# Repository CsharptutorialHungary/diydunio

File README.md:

# diydunio

A home makeable Arduino Uno clone

Part list: [parts.txt](parts.txt)

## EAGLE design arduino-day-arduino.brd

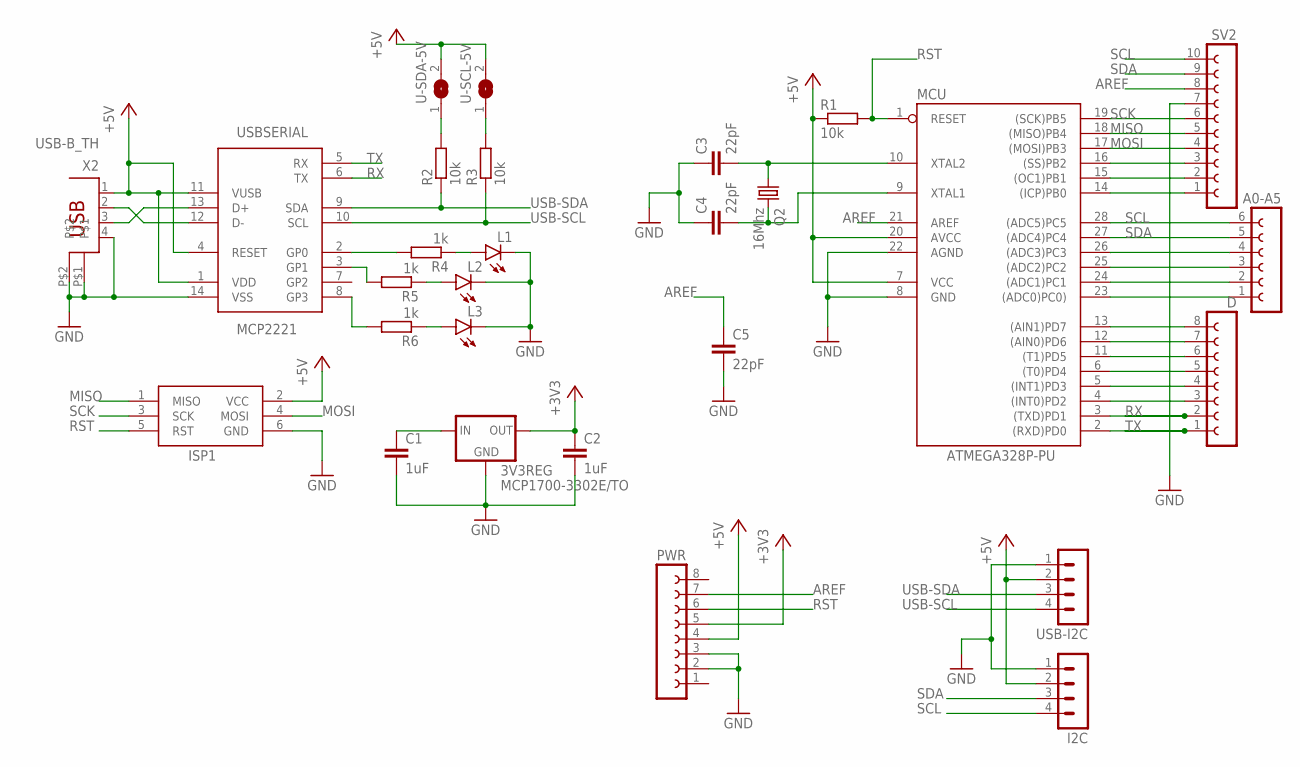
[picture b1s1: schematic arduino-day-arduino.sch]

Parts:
3V3REG: MCP1700-3302E/TO; TO92
A0-A5: FE06-1; FE06
C1, C2: 1uF; C025-025X050
C3, C4, C5: 22pF; C025-025X050
D: FE08-1; FE08
I2C: MA04-1
ISP1: AVRISP-6; AVRISP
L1, L2, L3: LED3MM
MCU: ATMEGA328P-PU; DIL28-3
PWR: FE08-1; FE08
Q2: 16Mhz; HC49/S
R1, R2, R3: 10k; 0204/7
R4, R5, R6: 1k; 0204/7
SV2: FE10-1; FE10
U-SCL-5V: SJW
U-SDA-5V: SJW
USB-I2C: MA04-1
USBSERIAL: MCP2221; DIL14
X2: USB-B_TH; PN61729

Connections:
+3V3: 3V3REG.3 (OUT), C2.1, PWR.5
+5V: I2C.2, ISP1.2 (VCC), MCU.7 (VCC), MCU.20 (AVCC), PWR.4, R1.1, U-SCL-5V.2, U-SDA-5V.2, USB-I2C.2, USBSERIAL.1 (VDD), USBSERIAL.4 (RESET), USBSERIAL.11 (VUSB), X2.1
AREF: C5.1, MCU.21 (AREF), PWR.7, SV2.8
GND: 3V3REG.1 (GND), C1.2, C2.2, C3.1, C4.1, C5.2, I2C.1, ISP1.6 (GND), L1.K (C), L2.K (C), L3.K (C), MCU.8 (GND), MCU.22 (AGND), PWR.2, PWR.3, SV2.7, USB-I2C.1, USBSERIAL.14 (VSS), X2.4, X2.P$1, X2.P$2
LED_RX: R4.2, USBSERIAL.2 (GP0)
LED_TX: R5.2, USBSERIAL.3 (GP1)
MISO: ISP1.1 (MISO), MCU.18 ((MISO)PB4), SV2.5
MOSI: ISP1.4 (MOSI), MCU.17 ((MOSI)PB3), SV2.4
unnamed: 3V3REG.2 (IN), C1.1
unnamed: D.3, MCU.4 ((INT0)PD2)
unnamed: D.4, MCU.5 ((INT1)PD3)
unnamed: D.5, MCU.6 ((T0)PD4)
unnamed: D.6, MCU.11 ((T1)PD5)
unnamed: D.7, MCU.12 ((AIN0)PD6)
unnamed: D.8, MCU.13 ((AIN1)PD7)
unnamed: A0-A5.1, MCU.23 ((ADC0)PC0))
unnamed: A0-A5.2, MCU.24 ((ADC1)PC1)
unnamed: A0-A5.3, MCU.25 ((ADC2)PC2)
unnamed: A0-A5.4, MCU.26 ((ADC3)PC3)
unnamed: MCU.14 ((ICP)PB0), SV2.1
unnamed: MCU.15 ((OC1)PB1), SV2.2
unnamed: MCU.16 ((SS)PB2), SV2.3
unnamed: R2.2, U-SDA-5V.1
unnamed: R3.2, U-SCL-5V.1
unnamed: USBSERIAL.12 (D-), X2.2
unnamed: USBSERIAL.13 (D+), X2.3
unnamed: L1.A, R4.1
unnamed: L2.A, R5.1
unnamed: L3.A, R6.1
unnamed: R6.2, USBSERIAL.8 (GP3)
unnamed: C3.2, MCU.10 (XTAL2), Q2.1
unnamed: C4.2, MCU.9 (XTAL1), Q2.2
RST: ISP1.5 (RST), MCU.1 (RESET), PWR.6, R1.2
RX: D.2, MCU.3 ((TXD)PD1), USBSERIAL.6 (TX)
SCK: ISP1.3 (SCK), MCU.19 ((SCK)PB5), SV2.6
SCL: A0-A5.6, I2C.4, MCU.28 ((ADC5)PC5), SV2.10
SDA: A0-A5.5, I2C.3, MCU.27 ((ADC4)PC4), SV2.9
TX: D.1, MCU.2 ((RXD)PD0), USBSERIAL.5 (RX)
USB-SCL: R3.1, USB-I2C.4, USBSERIAL.10 (SCL)
USB-SDA: R2.1, USB-I2C.3, USBSERIAL.9 (SDA)

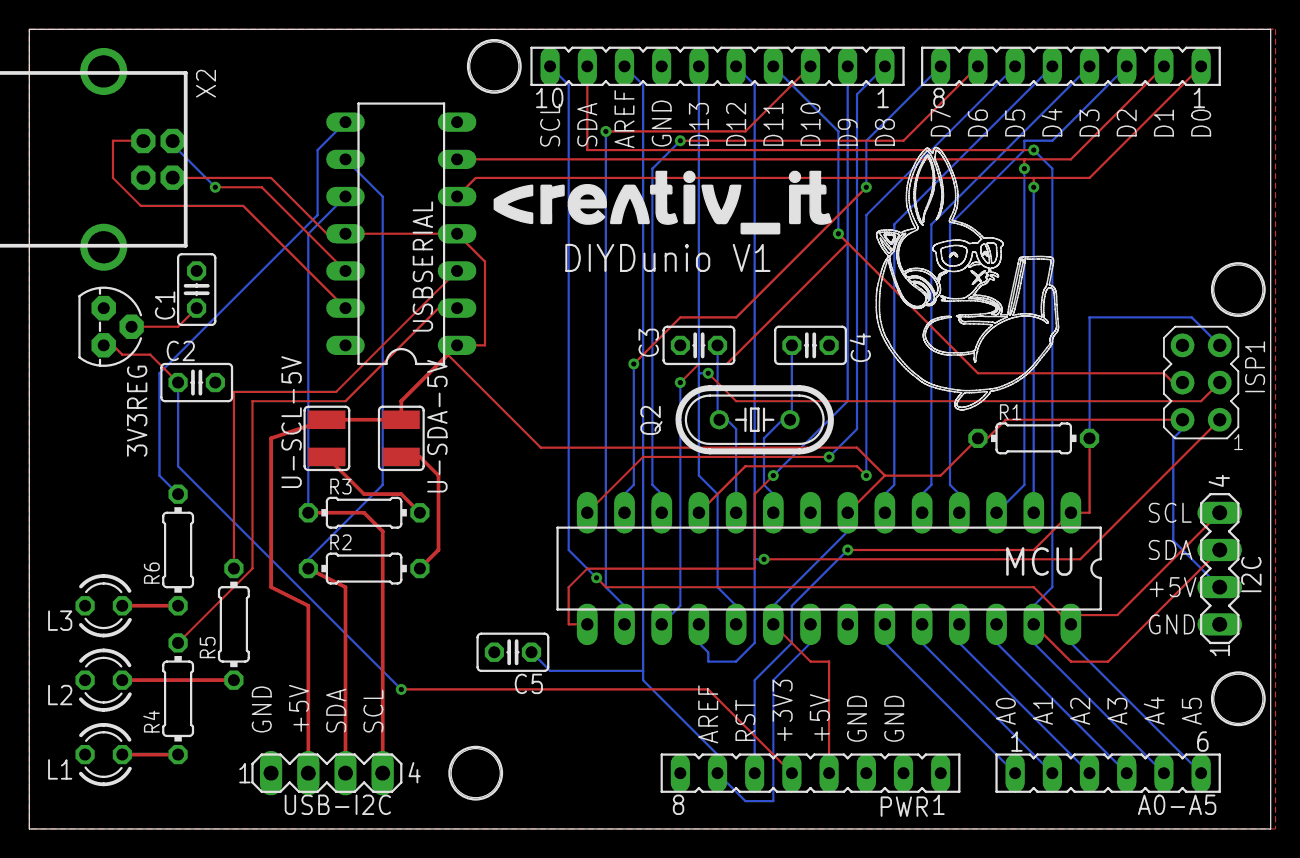
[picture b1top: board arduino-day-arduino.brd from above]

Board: 2 copper layers, 84.8 x 54.6 mm, 28 parts (0 on the bottom side), 40 nets.

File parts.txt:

Partlist

Exported from arduino-day-arduino.sch at 2024. 04. 23. 18:11

EAGLE Version 9.2.1 Copyright (c) 1988-2018 Autodesk, Inc.

Assembly variant: 

Part      Value            Device          Package      Library      Sheet

3V3REG    MCP1700-3302E/TO MCP1700TRI      TO92         adafruit     1
A0-A5                      FE06-1          FE06         con-lsta     1
C1        1uF              C-EU025-025X050 C025-025X050 rcl          1
C2        1uF              C-EU025-025X050 C025-025X050 rcl          1
C3        22pF             C-EU025-025X050 C025-025X050 rcl          1
C4        22pF             C-EU025-025X050 C025-025X050 rcl          1
C5        22pF             C-EU025-025X050 C025-025X050 rcl          1
D                          FE08-1          FE08         con-lsta     1
I2C                        MA04-1          MA04-1       con-lstb     1
ISP1      AVRISP-6         AVRISP-6        AVRISP       adafruit     1
L1                         LED3MM          LED3MM       led          1
L2                         LED3MM          LED3MM       led          1
L3                         LED3MM          LED3MM       led          1
MCU       ATMEGA328P-PU    ATMEGA328P-PU   DIL28-3      SmartPrj     1
PWR                        FE08-1          FE08         con-lsta     1
Q2        16Mhz            CRYSTALHC49S    HC49/S       crystal      1
R1        10k              R-EU_0204/7     0204/7       rcl          1
R2        10k              R-EU_0204/7     0204/7       rcl          1
R3        10k              R-EU_0204/7     0204/7       rcl          1
R4        1k               R-EU_0204/7     0204/7       rcl          1
R5        1k               R-EU_0204/7     0204/7       rcl          1
R6        1k               R-EU_0204/7     0204/7       rcl          1
SV2                        FE10-1          FE10         con-lsta     1
U-SCL-5V                   SJW             SJW          jumper       1
U-SDA-5V                   SJW             SJW          jumper       1
USB-I2C                    MA04-1          MA04-1       con-lstb     1
USBSERIAL MCP2221          MCP2221         DIL14        Webmaster442 1
X2        USB-B_TH         PN61729         PN61729      SmartPrj     1

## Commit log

2024-03-05 Schematic complete
2024-03-05 Homeduino
2024-03-10 Board layout
2024-03-10 Board routed
2024-04-03 Logok
2024-04-23 Orderable
2024-06-03 Workshop code
